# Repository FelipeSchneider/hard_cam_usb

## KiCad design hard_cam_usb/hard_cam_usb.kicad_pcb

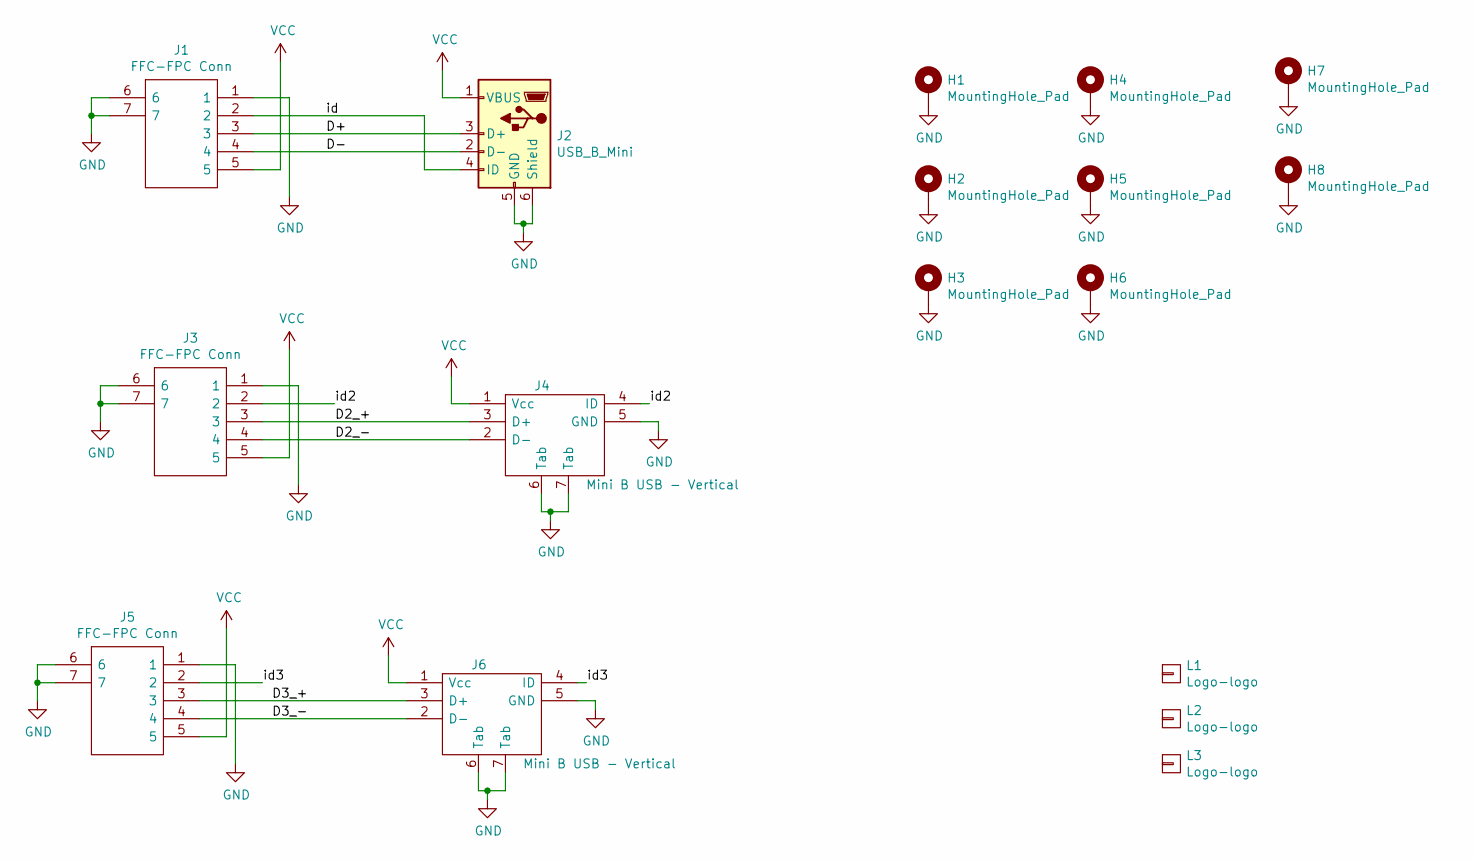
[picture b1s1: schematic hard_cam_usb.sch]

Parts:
H1, H2, H3, H4, H5, H6, H7, H8: MountingHole_Pad; MountingHole_3.2mm_M3_Pad_Via
J1, J3, J5: FFC-FPC Conn; 59453051110ECHLF; Part-Number 59453-051110ECHLF
J2: USB_B_Mini; USB_Mini-B_Wuerth_65100516121_Horizontal; Part-Number 65100516121
J4, J6: Mini B USB - Vertical; MUSB-B5-S-VT-TSMT-TR; Part-Number MUSB-B5-S-VT-TSMT-T/R
L1, L2, L3: Logo-logo; logo_vulcur

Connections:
/D2_+: J3.3, J4.3 (D+)
/D2_-: J3.4, J4.2 (D-)
/D3_+: J5.3, J6.3 (D+)
/D3_-: J5.4, J6.2 (D-)
/D+: J1.3, J2.3 (D+)
/D-: J1.4, J2.2 (D-)
/id: J1.2, J2.4 (ID)
/id2: J3.2, J4.4 (ID)
/id3: J5.2, J6.4 (ID)
GND: H1.1, H2.1, H3.1, H4.1, H5.1, H6.1, H7.1, H8.1, J1.1, J1.6, J1.7, J2.5 (GND), J2.6 (Shield), J3.1, J3.6, J3.7, J4.5 (GND), J4.6 (Tab), J4.7 (Tab), J5.1, J5.6, J5.7, J6.5 (GND), J6.6 (Tab), J6.7 (Tab)
VCC: J1.5, J2.1 (VBUS), J3.5, J4.1 (Vcc), J5.5, J6.1 (Vcc)

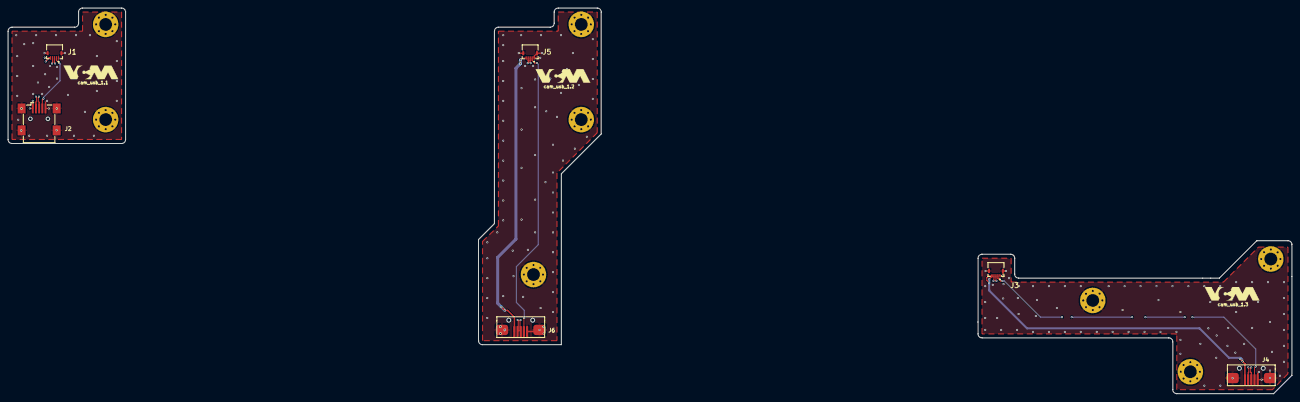
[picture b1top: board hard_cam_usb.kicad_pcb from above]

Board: 4 copper layers, 322.3 x 96.8 mm, 17 parts (0 on the bottom side), 11 nets.

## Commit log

2021-10-15 components and basic draw added
2021-10-15 Fixing the last commit
2021-10-19 sent to production
